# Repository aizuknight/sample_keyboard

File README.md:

# sample_keyboard
**sample_keyboard** is a keyboard with 6 keys to learn the basics of custom built keyboard design.

## License
Some of the CAD symbols and footprints in this repository were obtained from [SnapMagic Search](https://snapmagicsearch.com). These CAD files are licensed under the [Creative Commons Attribution-ShareAlike 4.0 International License (CC BY-SA)](https://creativecommons.org/licenses/by-sa/4.0/) with the [Design Exception 1.0](https://designexception.org/). Original design by SnapMagic Search and its original author.

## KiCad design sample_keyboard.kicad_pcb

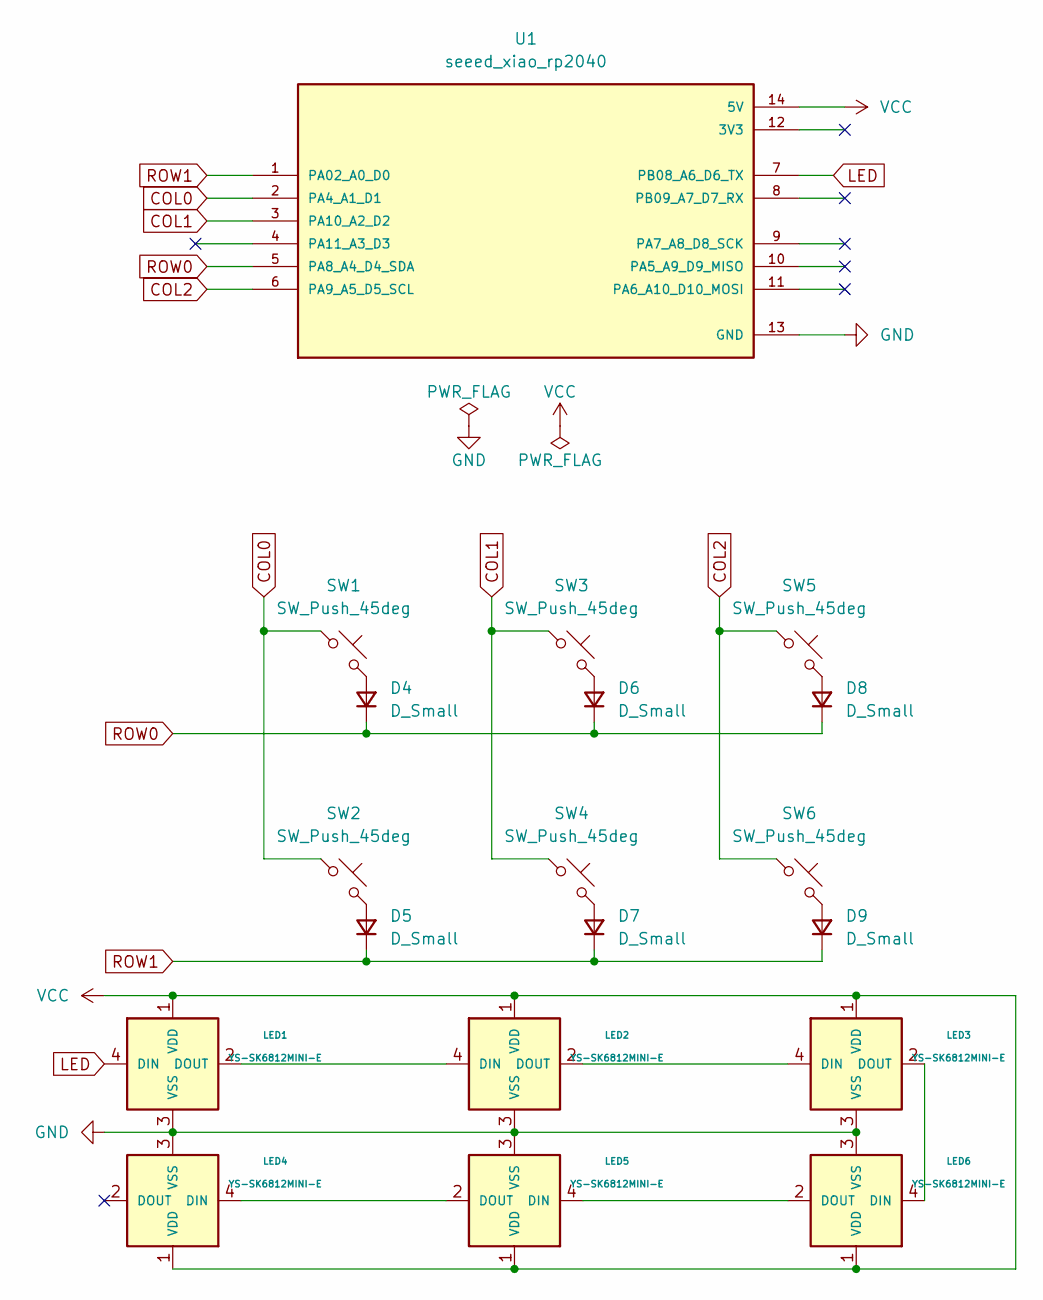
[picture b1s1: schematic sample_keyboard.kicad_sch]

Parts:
D4, D5, D6, D7, D8, D9: D_Small; D3_SMD_v2
LED1, LED2, LED3, LED4, LED5, LED6: YS-SK6812MINI-E
SW1, SW2, SW3, SW4, SW5, SW6: SW_Push_45deg; CherryMX_Hotswap
U1: seeed_xiao_rp2040; PARTREV N/A

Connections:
COL0: SW1.1, SW2.1, U1.2 (PA4_A1_D1)
COL1: SW3.1, SW4.1, U1.3 (PA10_A2_D2)
COL2: SW5.1, SW6.1, U1.6 (PA9_A5_D5_SCL)
GND: LED1.3 (VSS), LED2.3 (VSS), LED3.3 (VSS), LED4.3 (VSS), LED5.3 (VSS), LED6.3 (VSS), U1.13 (GND)
LED: LED1.4 (DIN), U1.7 (PB08_A6_D6_TX)
unnamed: D4.2 (A), SW1.2
unnamed: D5.2 (A), SW2.2
unnamed: D6.2 (A), SW3.2
unnamed: D7.2 (A), SW4.2
unnamed: D8.2 (A), SW5.2
unnamed: D9.2 (A), SW6.2
unnamed: LED1.2 (DOUT), LED2.4 (DIN)
unnamed: LED2.2 (DOUT), LED3.4 (DIN)
unnamed: LED3.2 (DOUT), LED6.4 (DIN)
unnamed: LED4.4 (DIN), LED5.2 (DOUT)
unnamed: LED5.4 (DIN), LED6.2 (DOUT)
ROW0: D4.1 (K), D6.1 (K), D8.1 (K), U1.5 (PA8_A4_D4_SDA)
ROW1: D5.1 (K), D7.1 (K), D9.1 (K), U1.1 (PA02_A0_D0)
VCC: LED1.1 (VDD), LED2.1 (VDD), LED3.1 (VDD), LED4.1 (VDD), LED5.1 (VDD), LED6.1 (VDD), U1.14 (5V)

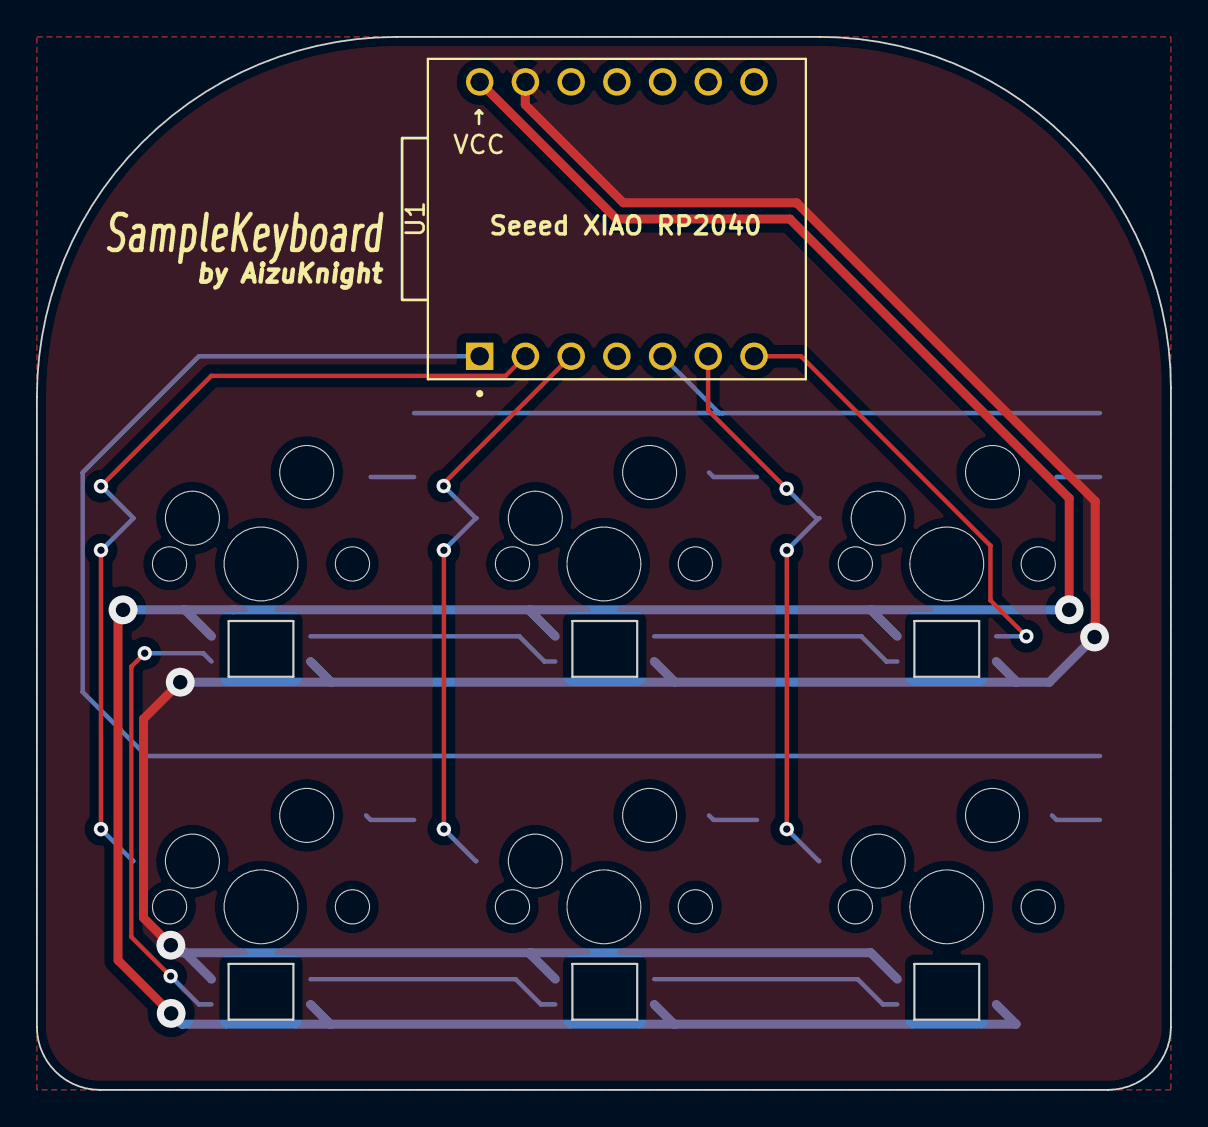
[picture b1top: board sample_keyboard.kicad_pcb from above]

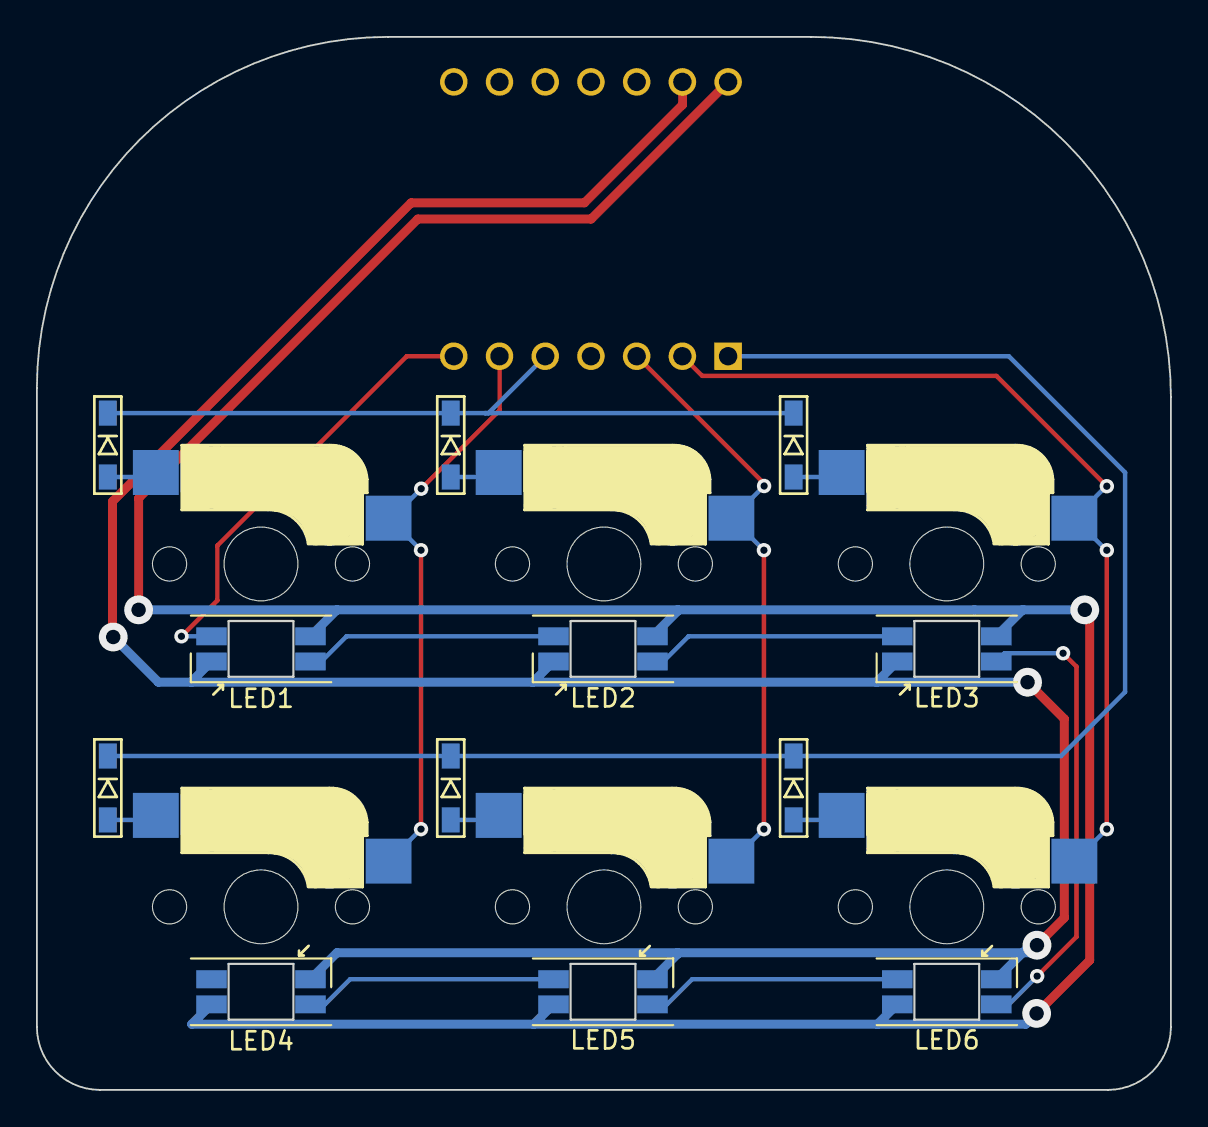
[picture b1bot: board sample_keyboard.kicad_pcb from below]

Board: 2 copper layers, 63.0 x 58.5 mm, 19 parts (12 on the bottom side), 19 nets.

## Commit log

2026-04-20 Move pcb design files to pcb directory
2026-04-20 Change description
